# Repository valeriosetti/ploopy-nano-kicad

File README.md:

# What's Ploopy Nano?

Ploopy nano is a compact trackball mouse whose hardware project (electronics & mechanics) is completely open source. The original github project can be found here:

<https://github.com/ploopyco/nano-trackball>

# Why a clone?

There are a couple of reasons for this:

1. Albeit the original project is open, it's designed for Altium software. The goal of this project is to clone that design as much as possible, but in KiCAD

1. Since I would like to test the BTU mod and I had that printed from an external online service, it didn't make much sense in my opinion to buy the whole kit just for the PCB. That's why I prefered to do it on my own

# What are the differences with the original design?

For technical and components' availability reasons, this design is slightly different from the original version. Here's the main points:

* USB typeC connector instead of microUSB
    * that's my preference
    * of course the USB speed is not changed, it's just a connector replacement
* debug UART pinheader
    * it's always useful to have it in case some debug is required
* replaced the 3x2 programmer's pinheader with TPs
    * this is mostly for layout reasons: on one hand the original connector required through holes, whereas TPs are just on one side; on the other hand it's also more flexible to place those 6 TPs
* smaller crystal (in size)
    * I could not find the original crystal available on JLCPCB, so I switched to an equivalent one which unfortunately has smaller footprint

# Board's design

The placement of componenets on the board was obtained using FreeCAD:

* I loaded PCB's step file into FreeCAD
* Generated a 2D top view of the PCB
* Exported into DXF
* Impoted the DXF into KiCAD

Similarly I did also for the layout of the PCB itself. In this case:

* I imported the layout of the board in FreeCAD using KiCadStepUp plugin
* Ridesigned the edges of the board
* Exported again into the *kicad_pcb* file
* Reopened KiCAD with new shape

# Extra

The **jlcpcb** folder contain gerber, BOM and placement files I used to order from JLCPCB site. They have been automatically generated from the specific KiCAD's extension.

Some components, likes the ATmega32U4 or the LED, are not present in the BOM because they're out of stock on JLCPCB, so I'm planning to buy them separately and solder manually.

# Results

Since the description is quite long I decided to create a specific [readme file](result/README.md) for this in order to explain also the step I did for the bringup.

# Final thoughts

Even thought it's a nice project, there are a few things which might be known for anyone who attempts at building it:

* the ADNS-5050 is absolutely impossible to find, at least here in Europe. I ended up buying the ADNS-5020 which is pin to pin compatible, but also for that one it was a mess: the 1st order from Aliexpress was lost somewhere and the 2nd one took some time to be delivered (which is not so common nowadays when buying from Aliexpress)
* the 38 mm (1.5 inches) ball is not easy to find as well. I know, those are used for small billiard balls, but if you don't want to buy an entire set of billiard ball for just using 1, then good luck in finding something

In general I strongly suggest to take a look and consider also 's projects:
* they are based on a RP2040 microcontroller, which you can find at almost the same price of the ATMEGA, but it's way more powerfull 
* he provides the project directly for KiCAD with also gerber files for JLCPCB--> https://github.com/jfedor2/rp2040-pmw3360
* he used another sensor, PMW3360, which seems way more easy to find online

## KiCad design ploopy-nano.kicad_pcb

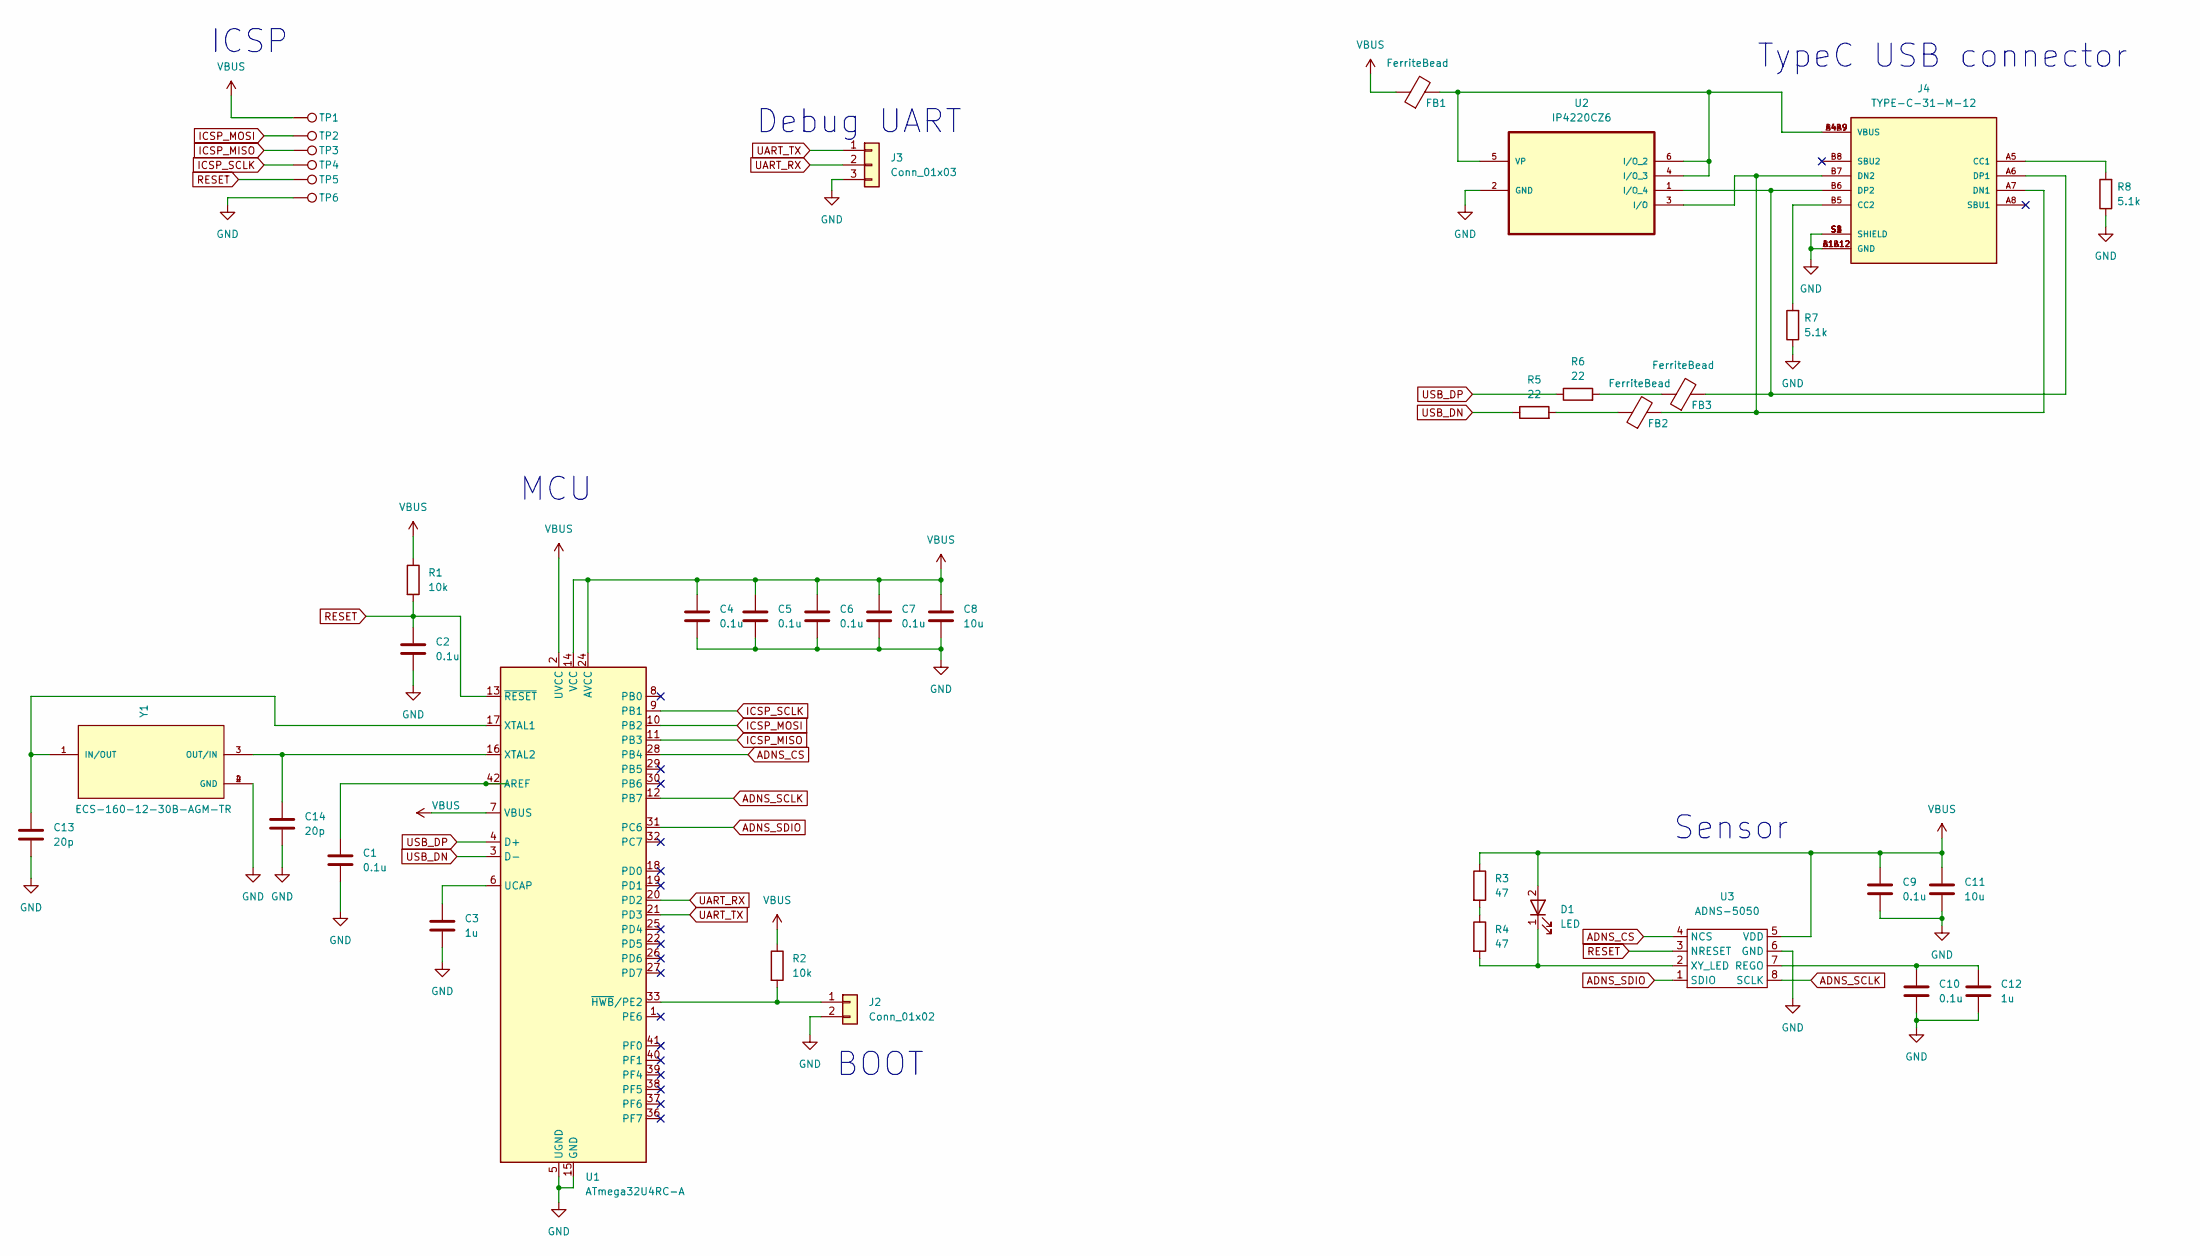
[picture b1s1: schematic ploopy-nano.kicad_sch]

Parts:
C1, C2, C4, C5, C6, C7, C9, C10: 0.1u; C_0603_1608Metric
C3, C12: 1u; C_0603_1608Metric
C8, C11: 10u; C_0603_1608Metric
C13, C14: 20p; C_0603_1608Metric
D1: LED; A67F
FB1, FB2, FB3: FerriteBead; R_0603_1608Metric
J2: Conn_01x02; PinHeader_1x02_P2.54mm_Vertical
J3: Conn_01x03; PinHeader_1x03_P2.54mm_Vertical
J4: TYPE-C-31-M-12; HRO_TYPE-C-31-M-12; PARTREV A
R1, R2: 10k; R_0603_1608Metric
R3, R4: 47; R_0603_1608Metric
R5, R6: 22; R_0603_1608Metric
R7, R8: 5.1k; R_0603_1608Metric
TP1, TP2, TP3, TP4, TP5, TP6: TestPoint; TestPoint_Pad_D1.0mm
U1: ATmega32U4RC-A; TQFP-44_10x10mm_P0.8mm
U2: IP4220CZ6; SOT95P275X110-6N; MPN IP4220CZ6
U3: ADNS-5050; ADNS-2610
Y1: ECS-160-12-30B-AGM-TR; Crystal_SMD_2520-4Pin_2.5x2.0mm

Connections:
ADNS_CS: U1.28 (PB4), U3.4 (NCS)
ADNS_SCLK: U1.12 (PB7), U3.8 (SCLK)
ADNS_SDIO: U1.31 (PC6), U3.1 (SDIO)
GND: C1.2, C2.2, C3.2, C4.2, C5.2, C6.2, C7.2, C8.2, C9.2, C10.2, C11.2, C12.2, C13.2, C14.2, J2.2, J3.3, J4.A1B12 (GND), J4.B1A12 (GND), J4.S1 (SHIELD), J4.S2 (SHIELD), J4.S3 (SHIELD), J4.S4 (SHIELD), R7.1, R8.1, TP6.1, U1.5 (UGND), U1.15 (GND), U1.23 (GND), U1.35 (GND), U1.43 (GND), U2.2 (GND), U3.6 (GND), Y1.2 (GND), Y1.4 (GND)
ICSP_MISO: TP3.1, U1.11 (PB3)
ICSP_MOSI: TP2.1, U1.10 (PB2)
ICSP_SCLK: TP4.1, U1.9 (PB1)
unnamed: C1.1, U1.42 (AREF)
unnamed: C3.1, U1.6 (UCAP)
unnamed: C10.1, C12.1, U3.7 (REGO)
unnamed: C13.1, U1.17 (XTAL1), Y1.1 (IN/OUT)
unnamed: C14.1, U1.16 (XTAL2), Y1.3 (OUT/IN)
unnamed: D1.1 (K), R4.2, U3.2 (XY_LED)
unnamed: FB1.2, J4.A4B9 (VBUS), J4.B4A9 (VBUS), U2.4 (I/O_3), U2.5 (VP), U2.6 (I/O_2)
unnamed: FB2.1, R5.2
unnamed: FB2.2, J4.A7 (DN1), J4.B7 (DN2), U2.3 (I/O)
unnamed: FB3.1, R6.2
unnamed: FB3.2, J4.A6 (DP1), J4.B6 (DP2), U2.1 (I/O_4)
unnamed: J2.1, R2.2, U1.33 (~HWB/PE2)
unnamed: J4.A5 (CC1), R8.2
unnamed: J4.B5 (CC2), R7.2
unnamed: R3.2, R4.1
RESET: C2.1, R1.2, TP5.1, U1.13 (~RESET), U3.3 (NRESET)
UART_RX: J3.2, U1.20 (PD2)
UART_TX: J3.1, U1.21 (PD3)
USB_DN: R5.1, U1.3 (D-)
USB_DP: R6.1, U1.4 (D+)
VBUS: C4.1, C5.1, C6.1, C7.1, C8.1, C9.1, C11.1, D1.2 (A), FB1.1, R1.1, R2.1, R3.1, TP1.1, U1.2 (UVCC), U1.7 (VBUS), U1.14 (VCC), U1.24 (AVCC), U1.34 (VCC), U1.44 (AVCC), U3.5 (VDD)

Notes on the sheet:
Debug UART
Sensor
BOOT
ICSP
TypeC USB connector
MCU

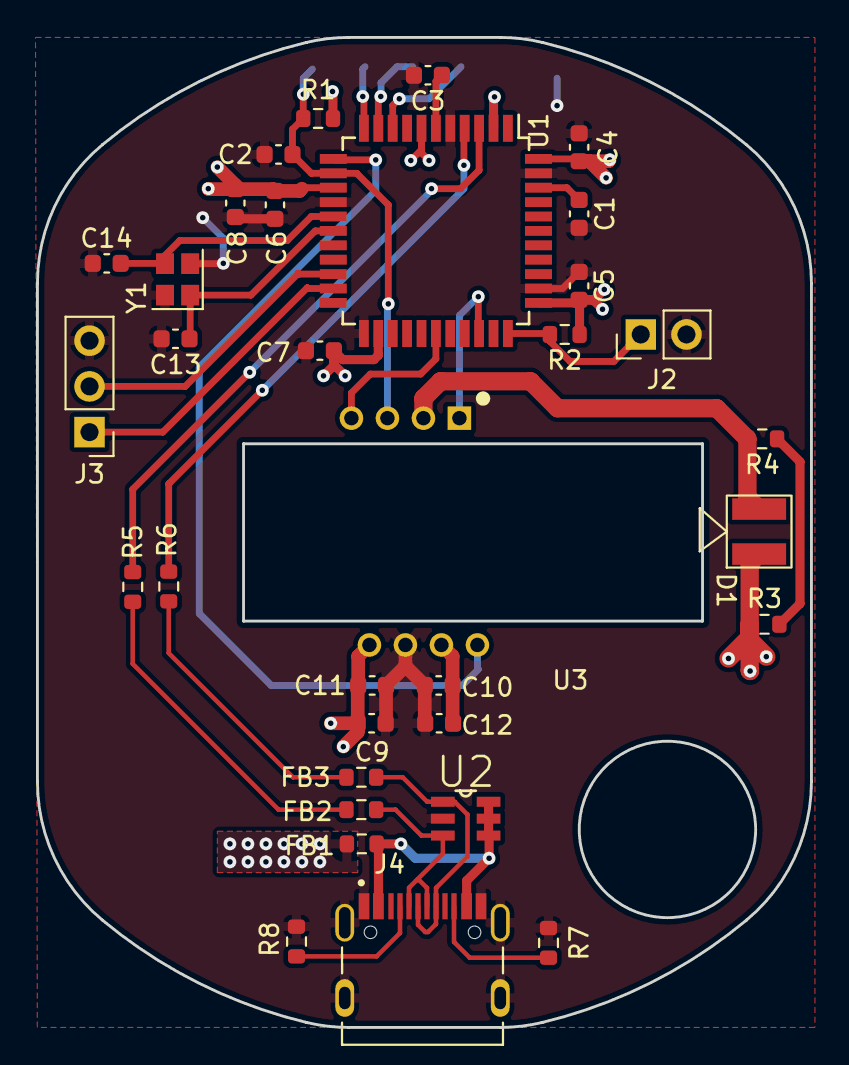
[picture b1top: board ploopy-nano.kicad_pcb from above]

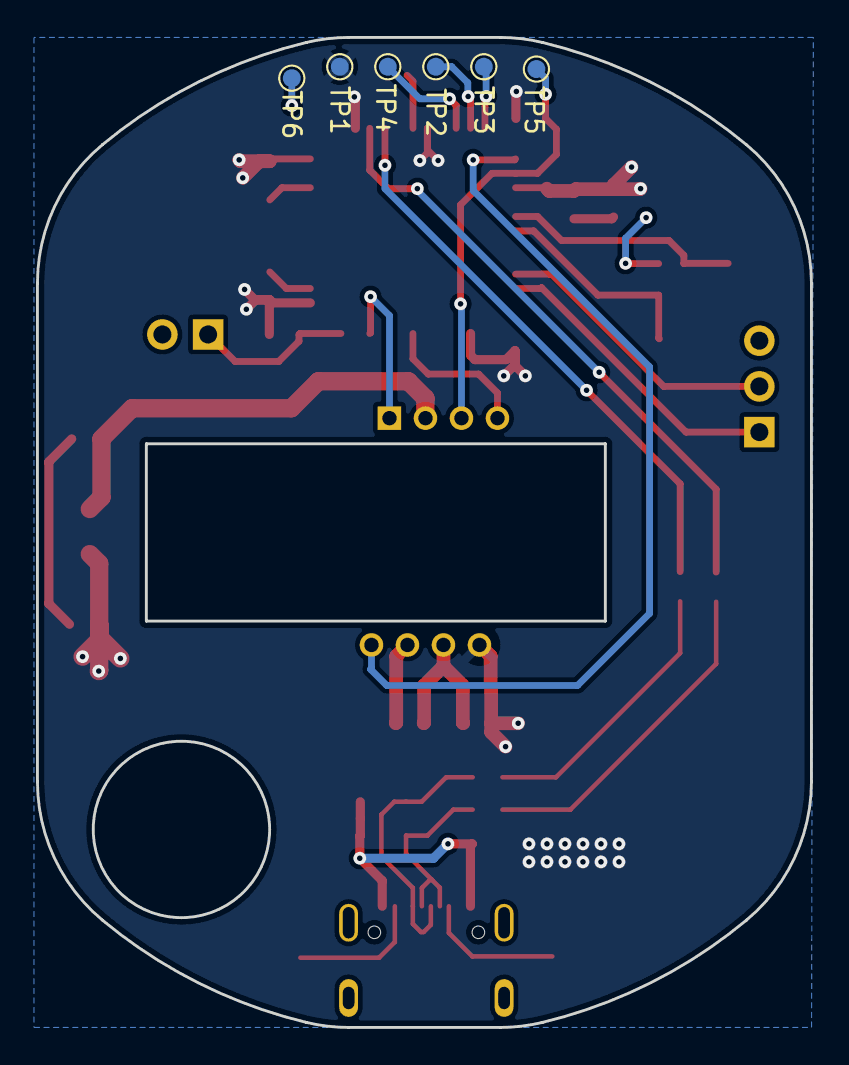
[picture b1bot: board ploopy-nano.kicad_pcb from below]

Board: 2 copper layers, 43.0 x 55.0 mm, 39 parts (6 on the bottom side), 28 nets.

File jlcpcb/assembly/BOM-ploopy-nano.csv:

Comment,Designator,Footprint,LCSC
FerriteBead,"FB1,FB2,FB3",R_0603_1608Metric,C107335
0.1u,"C1,C10,C2,C4,C5,C6,C7,C9",C_0603_1608Metric,C14663
1u,"C12,C3",C_0603_1608Metric,C15849
20p,"C13,C14",C_0603_1608Metric,C1603
TYPE-C-31-M-12,J4,HRO_TYPE-C-31-M-12,C165948
47,"R3,R4",R_0603_1608Metric,C23164
5.1k,"R7,R8",R_0603_1608Metric,C23186
22,"R5,R6",R_0603_1608Metric,C23345
10k,"R1,R2",R_0603_1608Metric,C25804
IP4220CZ6,U2,SOT95P275X110-6N,C558417
ECS-160-12-30B-AGM-TR,Y1,Crystal_SMD_2520-4Pin_2.5x2.0mm,C655061
10u,"C11,C8",C_0603_1608Metric,C96446

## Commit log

2022-10-11 pcb: removed bak files
2022-10-11 readme: updated with board's design details
2023-03-21 adding ADNS-5020 datasheet (because 5050 is impossible to find)
2023-03-21 updated main README file and created a new one for the results
2023-03-23 improved documentation
